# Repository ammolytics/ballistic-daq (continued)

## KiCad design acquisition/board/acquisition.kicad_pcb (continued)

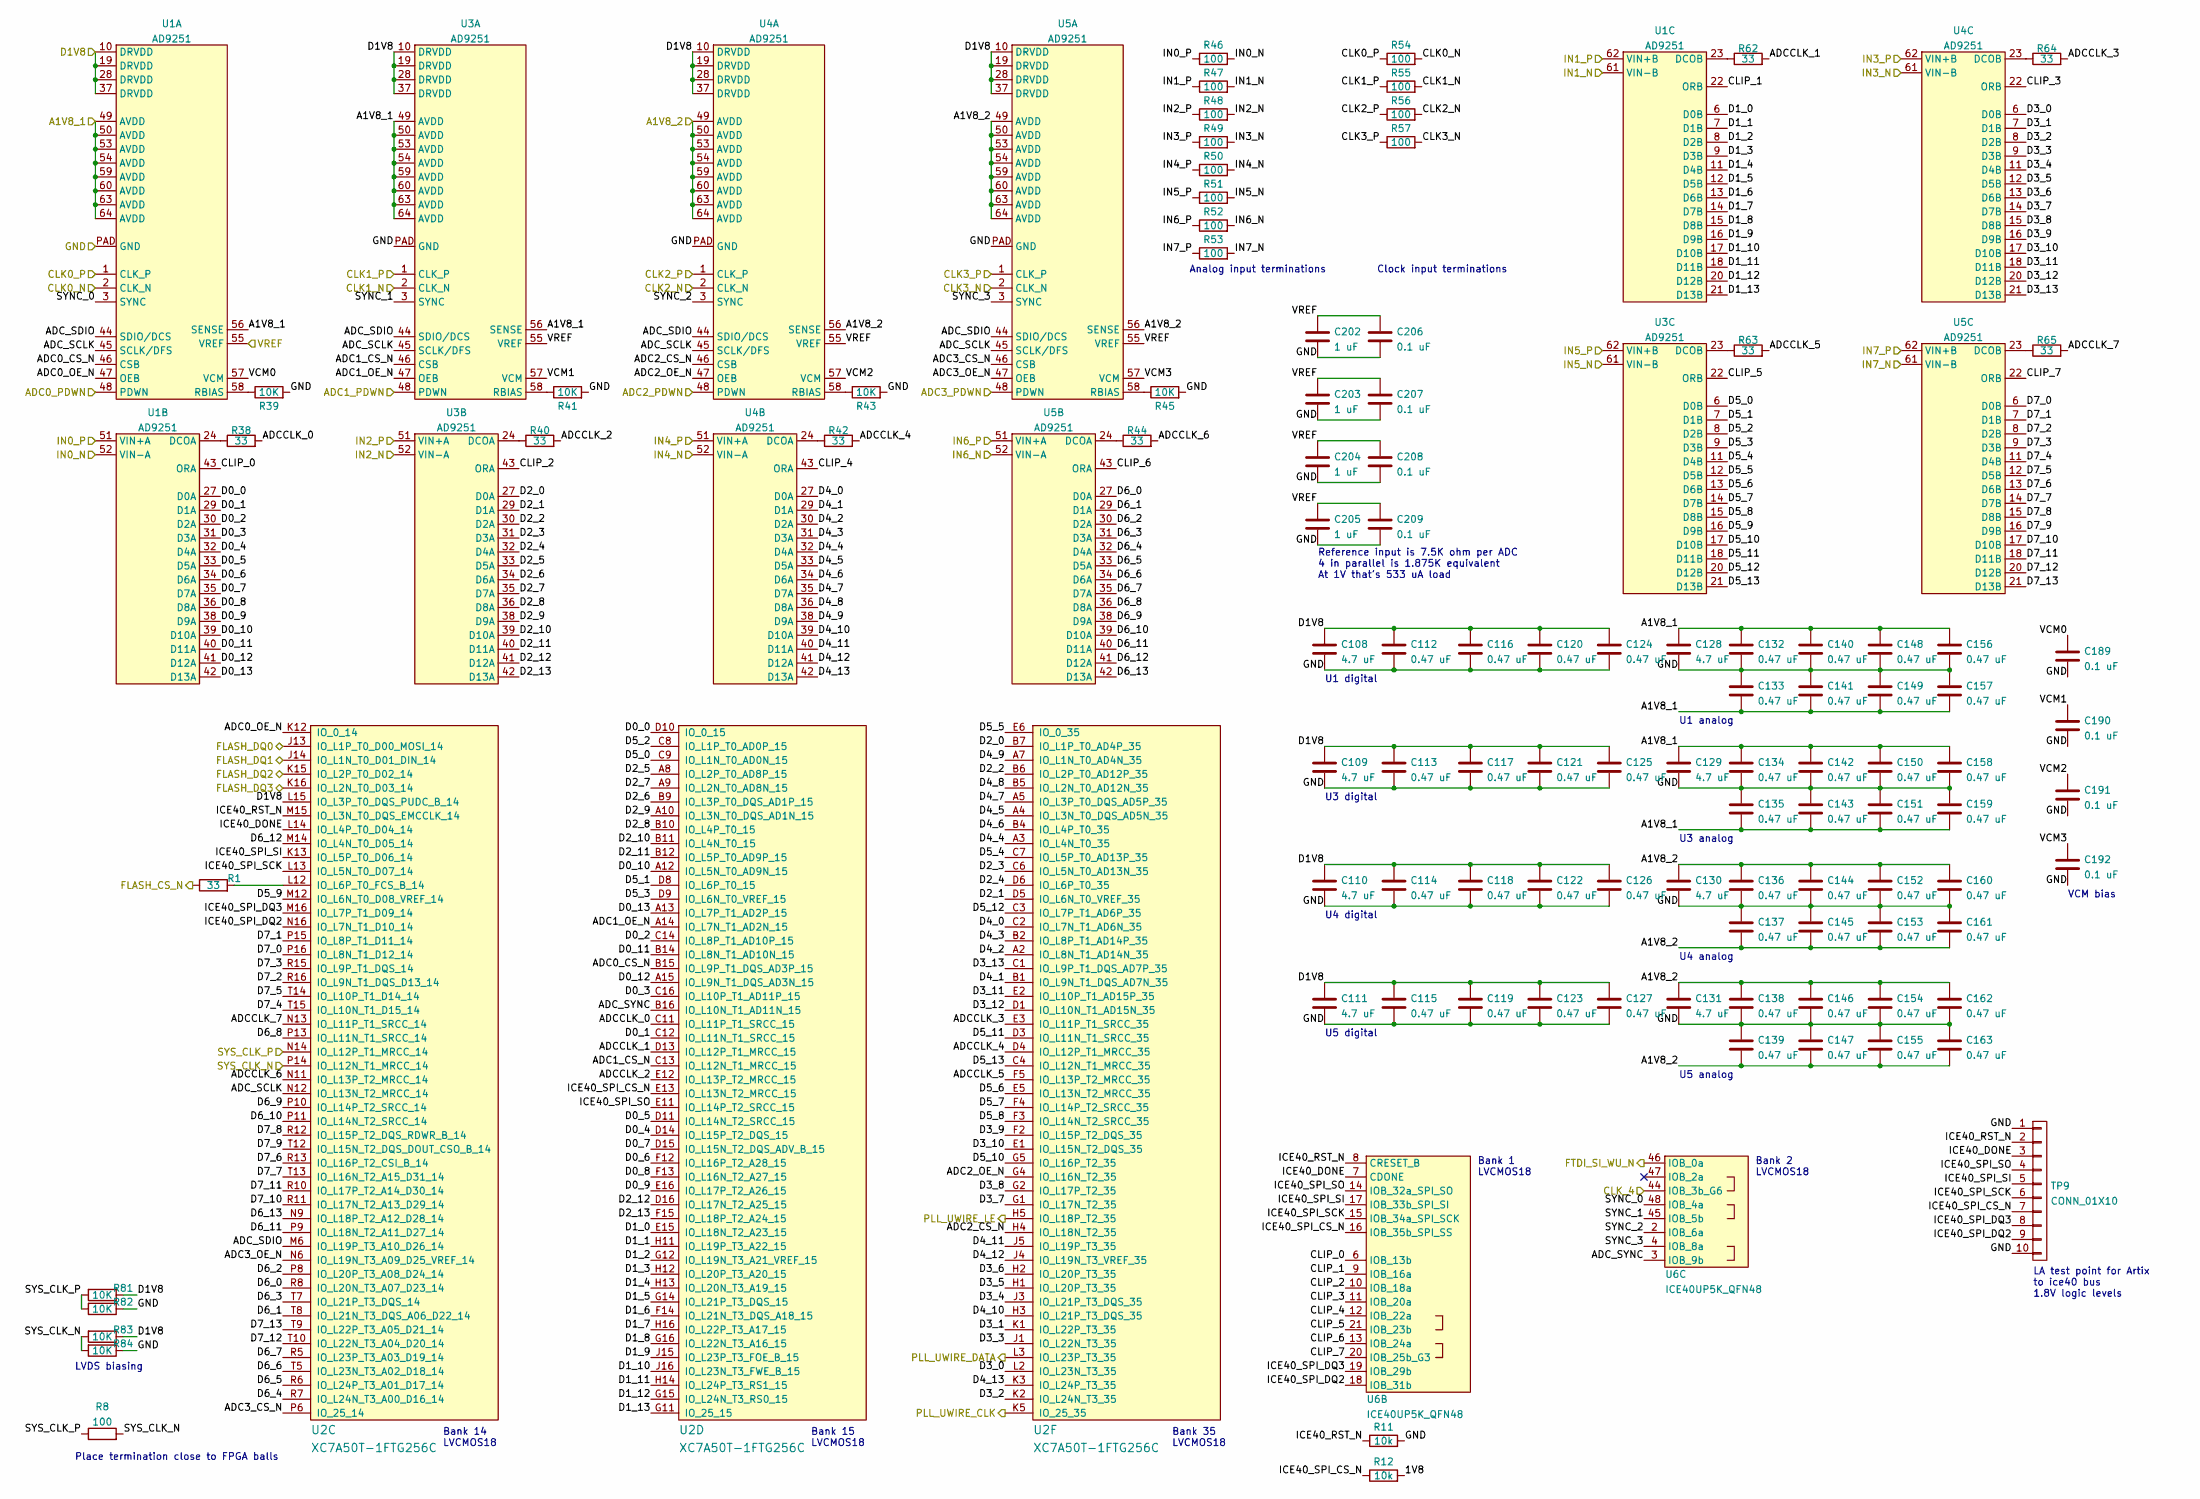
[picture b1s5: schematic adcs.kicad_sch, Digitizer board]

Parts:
C108, C109, C110, C111, C128, C129, C130, C131: 4.7 uF; EIA_0603_CAP_NOSILK
C112, C113, C114, C115, C116, C117, C118, C119, C120, C121, C122, C123, C124, C125, C126, C127, C132, C133, C134, C135, C136, C137, C138, C139, C140, C141, C142, C143, C144, C145, C146, C147, C148, C149, C150, C151, C152, C153, C154, C155, C156, C157, C158, C159, C160, C161, C162, C163: 0.47 uF; EIA_0402_CAP_NOSILK
C189, C190, C191, C192, C206, C207, C208, C209: 0.1 uF; EIA_0402_CAP_NOSILK
C202, C203, C204, C205: 1 uF; EIA_0603_CAP_NOSILK
R1, R38, R40, R42, R44, R62, R63, R64, R65: 33; EIA_0402_RES_NOSILK
R8, R46, R47, R48, R49, R50, R51, R52, R53, R54, R55, R56, R57: 100; EIA_0402_RES_NOSILK
R11, R12: 10k; EIA_0402_RES_NOSILK
R39, R41, R43, R45, R81, R82, R83, R84: 10K; EIA_0402_RES_NOSILK
TP9: CONN_01X10; CONN_HEADER_2.54MM_1x10
U1, U3, U4, U5: AD9251; QFN_64_0.5MM_9x9MM
U2: XC7A50T-1FTG256C; BGA_256_17x17_FULLARRAY_1MM_0.4MM_FTG256
U6: ICE40UP5K_QFN48; QFN_48_0.5MM_7x7MM

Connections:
/ADCs/1V8: R12.2
/ADCs/A1V8_1: C128.1, C129.1, C132.1, C133.2, C134.1, C135.2, C140.1, C141.2, C142.1, C143.2, C148.1, C149.2, C150.1, C151.2, C156.1, C157.2, C158.1, C159.2, U1.49 (AVDD), U1.50 (AVDD), U1.53 (AVDD), U1.54 (AVDD), U1.56 (SENSE), U1.59 (AVDD), U1.60 (AVDD), U1.63 (AVDD), U1.64 (AVDD), U3.49 (AVDD), U3.50 (AVDD), U3.53 (AVDD), U3.54 (AVDD), U3.56 (SENSE), U3.59 (AVDD), U3.60 (AVDD), U3.63 (AVDD), U3.64 (AVDD); also elsewhere on the board
/ADCs/A1V8_2: C130.1, C131.1, C136.1, C137.2, C138.1, C139.2, C144.1, C145.2, C146.1, C147.2, C152.1, C153.2, C154.1, C155.2, C160.1, C161.2, C162.1, C163.2, U4.49 (AVDD), U4.50 (AVDD), U4.53 (AVDD), U4.54 (AVDD), U4.56 (SENSE), U4.59 (AVDD), U4.60 (AVDD), U4.63 (AVDD), U4.64 (AVDD), U5.49 (AVDD), U5.50 (AVDD), U5.53 (AVDD), U5.54 (AVDD), U5.56 (SENSE), U5.59 (AVDD), U5.60 (AVDD), U5.63 (AVDD), U5.64 (AVDD); also elsewhere on the board
/ADCs/ADC0_CS_N: U1.46 (CSB), U2.B15 (IO_L9P_T1_DQS_AD3P_15)
/ADCs/ADC0_OE_N: U1.47 (OEB), U2.K12 (IO_0_14)
/ADCs/ADC1_CS_N: U2.C13 (IO_L12N_T1_MRCC_15), U3.46 (CSB)
/ADCs/ADC1_OE_N: U2.A14 (IO_L7N_T1_AD2N_15), U3.47 (OEB)
/ADCs/ADC2_CS_N: U2.H4 (IO_L18N_T2_35), U4.46 (CSB)
/ADCs/ADC2_OE_N: U2.G4 (IO_L16N_T2_35), U4.47 (OEB)
/ADCs/ADC3_CS_N: U2.P6 (IO_25_14), U5.46 (CSB)
/ADCs/ADC3_OE_N: U2.N6 (IO_L19N_T3_A09_D25_VREF_14), U5.47 (OEB)
/ADCs/ADCCLK_0: R38.2, U2.C11 (IO_L11P_T1_SRCC_15)
/ADCs/ADCCLK_1: R62.2, U2.D13 (IO_L12P_T1_MRCC_15)
/ADCs/ADCCLK_2: R40.2, U2.E12 (IO_L13P_T2_MRCC_15)
/ADCs/ADCCLK_3: R64.2, U2.E3 (IO_L11P_T1_SRCC_35)
/ADCs/ADCCLK_4: R42.2, U2.D4 (IO_L12P_T1_MRCC_35)
/ADCs/ADCCLK_5: R63.2, U2.F5 (IO_L13P_T2_MRCC_35)
/ADCs/ADCCLK_6: R44.2, U2.N11 (IO_L13P_T2_MRCC_14)
/ADCs/ADCCLK_7: R65.2, U2.N13 (IO_L11P_T1_SRCC_14)
/ADCs/ADC_SCLK: U1.45 (SCLK/DFS), U2.N12 (IO_L13N_T2_MRCC_14), U3.45 (SCLK/DFS), U4.45 (SCLK/DFS), U5.45 (SCLK/DFS)
/ADCs/ADC_SDIO: U1.44 (SDIO/DCS), U2.M6 (IO_L19P_T3_A10_D26_14), U3.44 (SDIO/DCS), U4.44 (SDIO/DCS), U5.44 (SDIO/DCS)
/ADCs/ADC_SYNC: U2.B16 (IO_L10N_T1_AD11N_15), U6.3 (IOB_9b)
/ADCs/CLIP_0: U1.43 (ORA), U6.6 (IOB_13b)
/ADCs/CLIP_1: U1.22 (ORB), U6.9 (IOB_16a)
/ADCs/CLIP_2: U3.43 (ORA), U6.10 (IOB_18a)
/ADCs/CLIP_3: U4.22 (ORB), U6.11 (IOB_20a)
/ADCs/CLIP_4: U4.43 (ORA), U6.12 (IOB_22a)
/ADCs/CLIP_5: U3.22 (ORB), U6.21 (IOB_23b)
/ADCs/CLIP_6: U5.43 (ORA), U6.13 (IOB_24a)
/ADCs/CLIP_7: U5.22 (ORB), U6.20 (IOB_25b_G3)
/ADCs/CLK0_N: R54.2, U1.2 (CLK_N); also elsewhere on the board
/ADCs/CLK0_P: R54.1, U1.1 (CLK_P); also elsewhere on the board
/ADCs/CLK1_N: R55.2, U3.2 (CLK_N); also elsewhere on the board
/ADCs/CLK1_P: R55.1, U3.1 (CLK_P); also elsewhere on the board
/ADCs/CLK2_N: R56.2, U4.2 (CLK_N); also elsewhere on the board
/ADCs/CLK2_P: R56.1, U4.1 (CLK_P); also elsewhere on the board
/ADCs/CLK3_N: R57.2, U5.2 (CLK_N); also elsewhere on the board
/ADCs/CLK3_P: R57.1, U5.1 (CLK_P); also elsewhere on the board
/ADCs/D0_0: U1.27 (D0A), U2.D10 (IO_0_15)
/ADCs/D0_1: U1.29 (D1A), U2.C12 (IO_L11N_T1_SRCC_15)
/ADCs/D0_2: U1.30 (D2A), U2.C14 (IO_L8P_T1_AD10P_15)
/ADCs/D0_3: U1.31 (D3A), U2.C16 (IO_L10P_T1_AD11P_15)
/ADCs/D0_4: U1.32 (D4A), U2.D14 (IO_L15P_T2_DQS_15)
/ADCs/D0_5: U1.33 (D5A), U2.D11 (IO_L14N_T2_SRCC_15)
/ADCs/D0_6: U1.34 (D6A), U2.F12 (IO_L16P_T2_A28_15)
/ADCs/D0_7: U1.35 (D7A), U2.D15 (IO_L15N_T2_DQS_ADV_B_15)
/ADCs/D0_8: U1.36 (D8A), U2.F13 (IO_L16N_T2_A27_15)
/ADCs/D0_9: U1.38 (D9A), U2.E16 (IO_L17P_T2_A26_15)
/ADCs/D0_10: U1.39 (D10A), U2.A12 (IO_L5N_T0_AD9N_15)
/ADCs/D0_11: U1.40 (D11A), U2.B14 (IO_L8N_T1_AD10N_15)
/ADCs/D0_12: U1.41 (D12A), U2.A15 (IO_L9N_T1_DQS_AD3N_15)
/ADCs/D0_13: U1.42 (D13A), U2.A13 (IO_L7P_T1_AD2P_15)
/ADCs/D1_0: U1.6 (D0B), U2.E15 (IO_L18N_T2_A23_15)
/ADCs/D1_1: U1.7 (D1B), U2.H11 (IO_L19P_T3_A22_15)
/ADCs/D1_2: U1.8 (D2B), U2.G12 (IO_L19N_T3_A21_VREF_15)
/ADCs/D1_3: U1.9 (D3B), U2.H12 (IO_L20P_T3_A20_15)
/ADCs/D1_4: U1.11 (D4B), U2.H13 (IO_L20N_T3_A19_15)
/ADCs/D1_5: U1.12 (D5B), U2.G14 (IO_L21P_T3_DQS_15)
/ADCs/D1_6: U1.13 (D6B), U2.F14 (IO_L21N_T3_DQS_A18_15)
/ADCs/D1_7: U1.14 (D7B), U2.H16 (IO_L22P_T3_A17_15)
/ADCs/D1_8: U1.15 (D8B), U2.G16 (IO_L22N_T3_A16_15)
/ADCs/D1_9: U1.16 (D9B), U2.J15 (IO_L23P_T3_FOE_B_15)
/ADCs/D1_10: U1.17 (D10B), U2.J16 (IO_L23N_T3_FWE_B_15)
/ADCs/D1_11: U1.18 (D11B), U2.H14 (IO_L24P_T3_RS1_15)
/ADCs/D1_12: U1.20 (D12B), U2.G15 (IO_L24N_T3_RS0_15)
/ADCs/D1_13: U1.21 (D13B), U2.G11 (IO_25_15)
/ADCs/D2_0: U2.B7 (IO_L1P_T0_AD4P_35), U3.27 (D0A)
/ADCs/D2_1: U2.D5 (IO_L6N_T0_VREF_35), U3.29 (D1A)
/ADCs/D2_2: U2.B6 (IO_L2P_T0_AD12P_35), U3.30 (D2A)
/ADCs/D2_3: U2.C6 (IO_L5N_T0_AD13N_35), U3.31 (D3A)
/ADCs/D2_4: U2.D6 (IO_L6P_T0_35), U3.32 (D4A)
/ADCs/D2_5: U2.A8 (IO_L2P_T0_AD8P_15), U3.33 (D5A)
/ADCs/D2_6: U2.B9 (IO_L3P_T0_DQS_AD1P_15), U3.34 (D6A)
/ADCs/D2_7: U2.A9 (IO_L2N_T0_AD8N_15), U3.35 (D7A)
/ADCs/D2_8: U2.B10 (IO_L4P_T0_15), U3.36 (D8A)
/ADCs/D2_9: U2.A10 (IO_L3N_T0_DQS_AD1N_15), U3.38 (D9A)
/ADCs/D2_10: U2.B11 (IO_L4N_T0_15), U3.39 (D10A)
/ADCs/D2_11: U2.B12 (IO_L5P_T0_AD9P_15), U3.40 (D11A)
/ADCs/D2_12: U2.D16 (IO_L17N_T2_A25_15), U3.41 (D12A)
/ADCs/D2_13: U2.F15 (IO_L18P_T2_A24_15), U3.42 (D13A)
/ADCs/D3_0: U2.L2 (IO_L23N_T3_35), U4.6 (D0B)
/ADCs/D3_1: U2.K1 (IO_L22P_T3_35), U4.7 (D1B)
/ADCs/D3_2: U2.K2 (IO_L24N_T3_35), U4.8 (D2B)
/ADCs/D3_3: U2.J1 (IO_L22N_T3_35), U4.9 (D3B)
/ADCs/D3_4: U2.J3 (IO_L21P_T3_DQS_35), U4.11 (D4B)
/ADCs/D3_5: U2.H1 (IO_L20P_T3_35), U4.12 (D5B)
/ADCs/D3_6: U2.H2 (IO_L20P_T3_35), U4.13 (D6B)
/ADCs/D3_7: U2.G1 (IO_L17N_T2_35), U4.14 (D7B)
/ADCs/D3_8: U2.G2 (IO_L17P_T2_35), U4.15 (D8B)
/ADCs/D3_9: U2.F2 (IO_L15P_T2_DQS_35), U4.16 (D9B)
/ADCs/D3_10: U2.E1 (IO_L15N_T2_DQS_35), U4.17 (D10B)
/ADCs/D3_11: U2.E2 (IO_L10P_T1_AD15P_35), U4.18 (D11B)
/ADCs/D3_12: U2.D1 (IO_L10N_T1_AD15N_35), U4.20 (D12B)
/ADCs/D3_13: U2.C1 (IO_L9P_T1_DQS_AD7P_35), U4.21 (D13B)
/ADCs/D4_0: U2.C2 (IO_L7N_T1_AD6N_35), U4.27 (D0A)
/ADCs/D4_1: U2.B1 (IO_L9N_T1_DQS_AD7N_35), U4.29 (D1A)
/ADCs/D4_2: U2.A2 (IO_L8N_T1_AD14N_35), U4.30 (D2A)
/ADCs/D4_3: U2.B2 (IO_L8P_T1_AD14P_35), U4.31 (D3A)
/ADCs/D4_4: U2.A3 (IO_L4N_T0_35), U4.32 (D4A)
/ADCs/D4_5: U2.A4 (IO_L3N_T0_DQS_AD5N_35), U4.33 (D5A)
/ADCs/D4_6: U2.B4 (IO_L4P_T0_35), U4.34 (D6A)
/ADCs/D4_7: U2.A5 (IO_L3P_T0_DQS_AD5P_35), U4.35 (D7A)
/ADCs/D4_8: U2.B5 (IO_L2N_T0_AD12N_35), U4.36 (D8A)
/ADCs/D4_9: U2.A7 (IO_L1N_T0_AD4N_35), U4.38 (D9A)
/ADCs/D4_10: U2.H3 (IO_L21P_T3_DQS_35), U4.39 (D10A)
/ADCs/D4_11: U2.J5 (IO_L19P_T3_35), U4.40 (D11A)
/ADCs/D4_12: U2.J4 (IO_L19N_T3_VREF_35), U4.41 (D12A)
/ADCs/D4_13: U2.K3 (IO_L24P_T3_35), U4.42 (D13A)
/ADCs/D5_0: U2.C9 (IO_L1N_T0_AD0N_15), U3.6 (D0B)
/ADCs/D5_1: U2.D8 (IO_L6P_T0_15), U3.7 (D1B)
/ADCs/D5_2: U2.C8 (IO_L1P_T0_AD0P_15), U3.8 (D2B)
/ADCs/D5_3: U2.D9 (IO_L6N_T0_VREF_15), U3.9 (D3B)
/ADCs/D5_4: U2.C7 (IO_L5P_T0_AD13P_35), U3.11 (D4B)
/ADCs/D5_5: U2.E6 (IO_0_35), U3.12 (D5B)
/ADCs/D5_6: U2.E5 (IO_L13N_T2_MRCC_35), U3.13 (D6B)
/ADCs/D5_7: U2.F4 (IO_L14P_T2_SRCC_35), U3.14 (D7B)
/ADCs/D5_8: U2.F3 (IO_L14N_T2_SRCC_35), U3.15 (D8B)
/ADCs/D5_9: U2.M12 (IO_L6N_T0_D08_VREF_14), U3.16 (D9B)
/ADCs/D5_10: U2.G5 (IO_L16P_T2_35), U3.17 (D10B)
/ADCs/D5_11: U2.D3 (IO_L11N_T1_SRCC_35), U3.18 (D11B)
/ADCs/D5_12: U2.C3 (IO_L7P_T1_AD6P_35), U3.20 (D12B)
/ADCs/D5_13: U2.C4 (IO_L12N_T1_MRCC_35), U3.21 (D13B)
/ADCs/D6_0: U2.R8 (IO_L20N_T3_A07_D23_14), U5.27 (D0A)
/ADCs/D6_1: U2.T8 (IO_L21N_T3_DQS_A06_D22_14), U5.29 (D1A)
/ADCs/D6_2: U2.P8 (IO_L20P_T3_A08_D24_14), U5.30 (D2A)
/ADCs/D6_3: U2.T7 (IO_L21P_T3_DQS_14), U5.31 (D3A)
/ADCs/D6_4: U2.R7 (IO_L24N_T3_A00_D16_14), U5.32 (D4A)
/ADCs/D6_5: U2.R6 (IO_L24P_T3_A01_D17_14), U5.33 (D5A)
/ADCs/D6_6: U2.T5 (IO_L23N_T3_A02_D18_14), U5.34 (D6A)
/ADCs/D6_7: U2.R5 (IO_L23P_T3_A03_D19_14), U5.35 (D7A)
/ADCs/D6_8: U2.P13 (IO_L11N_T1_SRCC_14), U5.36 (D8A)
/ADCs/D6_9: U2.P10 (IO_L14P_T2_SRCC_14), U5.38 (D9A)
/ADCs/D6_10: U2.P11 (IO_L14N_T2_SRCC_14), U5.39 (D10A)
/ADCs/D6_11: U2.P9 (IO_L18N_T2_A11_D27_14), U5.40 (D11A)
/ADCs/D6_12: U2.M14 (IO_L4N_T0_D05_14), U5.41 (D12A)
/ADCs/D6_13: U2.N9 (IO_L18P_T2_A12_D28_14), U5.42 (D13A)
/ADCs/D7_0: U2.P16 (IO_L8N_T1_D12_14), U5.6 (D0B)
/ADCs/D7_1: U2.P15 (IO_L8P_T1_D11_14), U5.7 (D1B)
/ADCs/D7_2: U2.R16 (IO_L9N_T1_DQS_D13_14), U5.8 (D2B)
/ADCs/D7_3: U2.R15 (IO_L9P_T1_DQS_14), U5.9 (D3B)
/ADCs/D7_4: U2.T15 (IO_L10N_T1_D15_14), U5.11 (D4B)
/ADCs/D7_5: U2.T14 (IO_L10P_T1_D14_14), U5.12 (D5B)
/ADCs/D7_6: U2.R13 (IO_L16P_T2_CSI_B_14), U5.13 (D6B)
/ADCs/D7_7: U2.T13 (IO_L16N_T2_A15_D31_14), U5.14 (D7B)
/ADCs/D7_8: U2.R12 (IO_L15P_T2_DQS_RDWR_B_14), U5.15 (D8B)
/ADCs/D7_9: U2.T12 (IO_L15N_T2_DQS_DOUT_CSO_B_14), U5.16 (D9B)
/ADCs/D7_10: U2.R11 (IO_L17N_T2_A13_D29_14), U5.17 (D10B)
/ADCs/D7_11: U2.R10 (IO_L17P_T2_A14_D30_14), U5.18 (D11B)
/ADCs/D7_12: U2.T10 (IO_L22N_T3_A04_D20_14), U5.20 (D12B)
/ADCs/D7_13: U2.T9 (IO_L22P_T3_A05_D21_14), U5.21 (D13B)
/ADCs/FLASH_DQ0: U2.J13 (IO_L1P_T0_D00_MOSI_14); also elsewhere on the board
/ADCs/FLASH_DQ1: U2.J14 (IO_L1N_T0_D01_DIN_14); also elsewhere on the board
/ADCs/FLASH_DQ2: U2.K15 (IO_L2P_T0_D02_14); also elsewhere on the board
/ADCs/FLASH_DQ3: U2.K16 (IO_L2N_T0_D03_14); also elsewhere on the board
/ADCs/FTDI_SI_WU_N: U6.46 (IOB_0a); also elsewhere on the board
/ADCs/ICE40_DONE: TP9.3, U2.L14 (IO_L4P_T0_D04_14), U6.7 (CDONE)
/ADCs/ICE40_RST_N: R11.1, TP9.2, U2.M15 (IO_L3N_T0_DQS_EMCCLK_14), U6.8 (CRESET_B)
/ADCs/ICE40_SPI_CS_N: R12.1, TP9.7, U2.E13 (IO_L13N_T2_MRCC_15), U6.16 (IOB_35b_SPI_SS)
/ADCs/ICE40_SPI_DQ2: TP9.9, U2.N16 (IO_L7N_T1_D10_14), U6.18 (IOB_31b)
/ADCs/ICE40_SPI_DQ3: TP9.8, U2.M16 (IO_L7P_T1_D09_14), U6.19 (IOB_29b)
/ADCs/ICE40_SPI_SCK: TP9.6, U2.L13 (IO_L5N_T0_D07_14), U6.15 (IOB_34a_SPI_SCK)
/ADCs/ICE40_SPI_SI: TP9.5, U2.K13 (IO_L5P_T0_D06_14), U6.17 (IOB_33b_SPI_SI)
/ADCs/ICE40_SPI_SO: TP9.4, U2.E11 (IO_L14P_T2_SRCC_15), U6.14 (IOB_32a_SPI_SO)
/ADCs/IN0_N: R46.2, U1.52 (VIN-A); also elsewhere on the board
/ADCs/IN0_P: R46.1, U1.51 (VIN+A); also elsewhere on the board
/ADCs/IN1_N: R47.2, U1.61 (VIN-B); also elsewhere on the board
/ADCs/IN1_P: R47.1, U1.62 (VIN+B); also elsewhere on the board
/ADCs/IN2_N: R48.2, U3.52 (VIN-A); also elsewhere on the board
/ADCs/IN2_P: R48.1, U3.51 (VIN+A); also elsewhere on the board
/ADCs/IN3_N: R49.2, U4.61 (VIN-B); also elsewhere on the board
/ADCs/IN3_P: R49.1, U4.62 (VIN+B); also elsewhere on the board
/ADCs/IN4_N: R50.2, U4.52 (VIN-A); also elsewhere on the board
/ADCs/IN4_P: R50.1, U4.51 (VIN+A); also elsewhere on the board
/ADCs/IN5_N: R51.2, U3.61 (VIN-B); also elsewhere on the board
/ADCs/IN5_P: R51.1, U3.62 (VIN+B); also elsewhere on the board
/ADCs/IN6_N: R52.2, U5.52 (VIN-A); also elsewhere on the board
/ADCs/IN6_P: R52.1, U5.51 (VIN+A); also elsewhere on the board
/ADCs/IN7_N: R53.2, U5.61 (VIN-B); also elsewhere on the board
/ADCs/IN7_P: R53.1, U5.62 (VIN+B); also elsewhere on the board
/ADCs/PLL_UWIRE_CLK: U2.K5 (IO_25_35); also elsewhere on the board
/ADCs/PLL_UWIRE_DATA: U2.L3 (IO_L23P_T3_35); also elsewhere on the board
/ADCs/PLL_UWIRE_LE: U2.H5 (IO_L18P_T2_35); also elsewhere on the board
/ADCs/SYNC_0: U1.3 (SYNC), U6.48 (IOB_4a)
/ADCs/SYNC_1: U3.3 (SYNC), U6.45 (IOB_5b)
/ADCs/SYNC_2: U4.3 (SYNC), U6.2 (IOB_6a)
/ADCs/SYNC_3: U5.3 (SYNC), U6.4 (IOB_8a)
/ADCs/SYS_CLK_N: R8.2, R83.2, R84.2, U2.P14 (IO_L12N_T1_MRCC_14); also elsewhere on the board
/ADCs/SYS_CLK_P: R8.1, R81.2, R82.2, U2.N14 (IO_L12P_T1_MRCC_14); also elsewhere on the board
/ADCs/VCM0: C189.1, U1.57 (VCM)
/ADCs/VCM1: C190.1, U3.57 (VCM)
/ADCs/VCM2: C191.1, U4.57 (VCM)
/ADCs/VCM3: C192.1, U5.57 (VCM)
/CLK_4: U6.44 (IOB_3b_G6); also elsewhere on the board
/D1V8: C108.1, C109.1, C110.1, C111.1, C112.1, C113.1, C114.1, C115.1, C116.1, C117.1, C118.1, C119.1, C120.1, C121.1, C122.1, C123.1, C124.1, C125.1, C126.1, C127.1, R81.1, R83.1, U1.10 (DRVDD), U1.19 (DRVDD), U1.28 (DRVDD), U1.37 (DRVDD), U2.L15 (IO_L3P_T0_DQS_PUDC_B_14), U3.10 (DRVDD), U3.19 (DRVDD), U3.28 (DRVDD), U3.37 (DRVDD), U4.10 (DRVDD), U4.19 (DRVDD), U4.28 (DRVDD), U4.37 (DRVDD), U5.10 (DRVDD), U5.19 (DRVDD), U5.28 (DRVDD), U5.37 (DRVDD); also elsewhere on the board
/GND: C108.2, C109.2, C110.2, C111.2, C112.2, C113.2, C114.2, C115.2, C116.2, C117.2, C118.2, C119.2, C120.2, C121.2, C122.2, C123.2, C124.2, C125.2, C126.2, C127.2, C128.2, C129.2, C130.2, C131.2, C132.2, C133.1, C134.2, C135.1, C136.2, C137.1, C138.2, C139.1, C140.2, C141.1, C142.2, C143.1, C144.2, C145.1, C146.2, C147.1, C148.2, C149.1, C150.2, C151.1, C152.2, C153.1, C154.2, C155.1, C156.2, C157.1, C158.2, C159.1, C160.2, C161.1, C162.2, C163.1, C189.2, C190.2, C191.2, C192.2, C202.2, C203.2, C204.2, C205.2, C206.2, C207.2, C208.2, C209.2, R11.2, R39.2, R41.2, R43.2, R45.2, R82.1, R84.1, TP9.1, TP9.10, U1.PAD (GND), U3.PAD (GND), U4.PAD (GND), U5.PAD (GND); also elsewhere on the board
/MCU/ADC0_PDWN: U1.48 (PDWN); also elsewhere on the board
/MCU/ADC1_PDWN: U3.48 (PDWN); also elsewhere on the board
/MCU/ADC2_PDWN: U4.48 (PDWN); also elsewhere on the board
/MCU/ADC3_PDWN: U5.48 (PDWN); also elsewhere on the board
/QSPI flash/FLASH_CS_N: R1.1; also elsewhere on the board
/VREF: C202.1, C203.1, C204.1, C205.1, C206.1, C207.1, C208.1, C209.1, U1.55 (VREF), U3.55 (VREF), U4.55 (VREF), U5.55 (VREF); also elsewhere on the board
unnamed: R1.2, U2.L12 (IO_L6P_T0_FCS_B_14)
unnamed: R38.1, U1.24 (DCOA)
unnamed: R39.1, U1.58 (RBIAS)
unnamed: R40.1, U3.24 (DCOA)
unnamed: R41.1, U3.58 (RBIAS)
unnamed: R42.1, U4.24 (DCOA)
unnamed: R43.1, U4.58 (RBIAS)
unnamed: R44.1, U5.24 (DCOA)
unnamed: R45.1, U5.58 (RBIAS)
unnamed: R62.1, U1.23 (DCOB)
unnamed: R63.1, U3.23 (DCOB)
unnamed: R64.1, U4.23 (DCOB)
unnamed: R65.1, U5.23 (DCOB)

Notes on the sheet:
Bank 35 LVCMOS18
U5 analog
Bank 15 LVCMOS18
LVDS biasing
Bank 2 LVCMOS18
Bank 14 LVCMOS18
U4 analog
U4 digital
Analog input terminations
Clock input terminations
Bank 1 LVCMOS18
Place termination close to FPGA balls
VCM bias
U3 analog
Reference input is 7.5K ohm per ADC 4 in parallel is 1.875K equivalent At 1V that's 533 uA load
LA test point for Artix to ice40 bus 1.8V logic levels
U1 digital
U3 digital
U5 digital
U1 analog

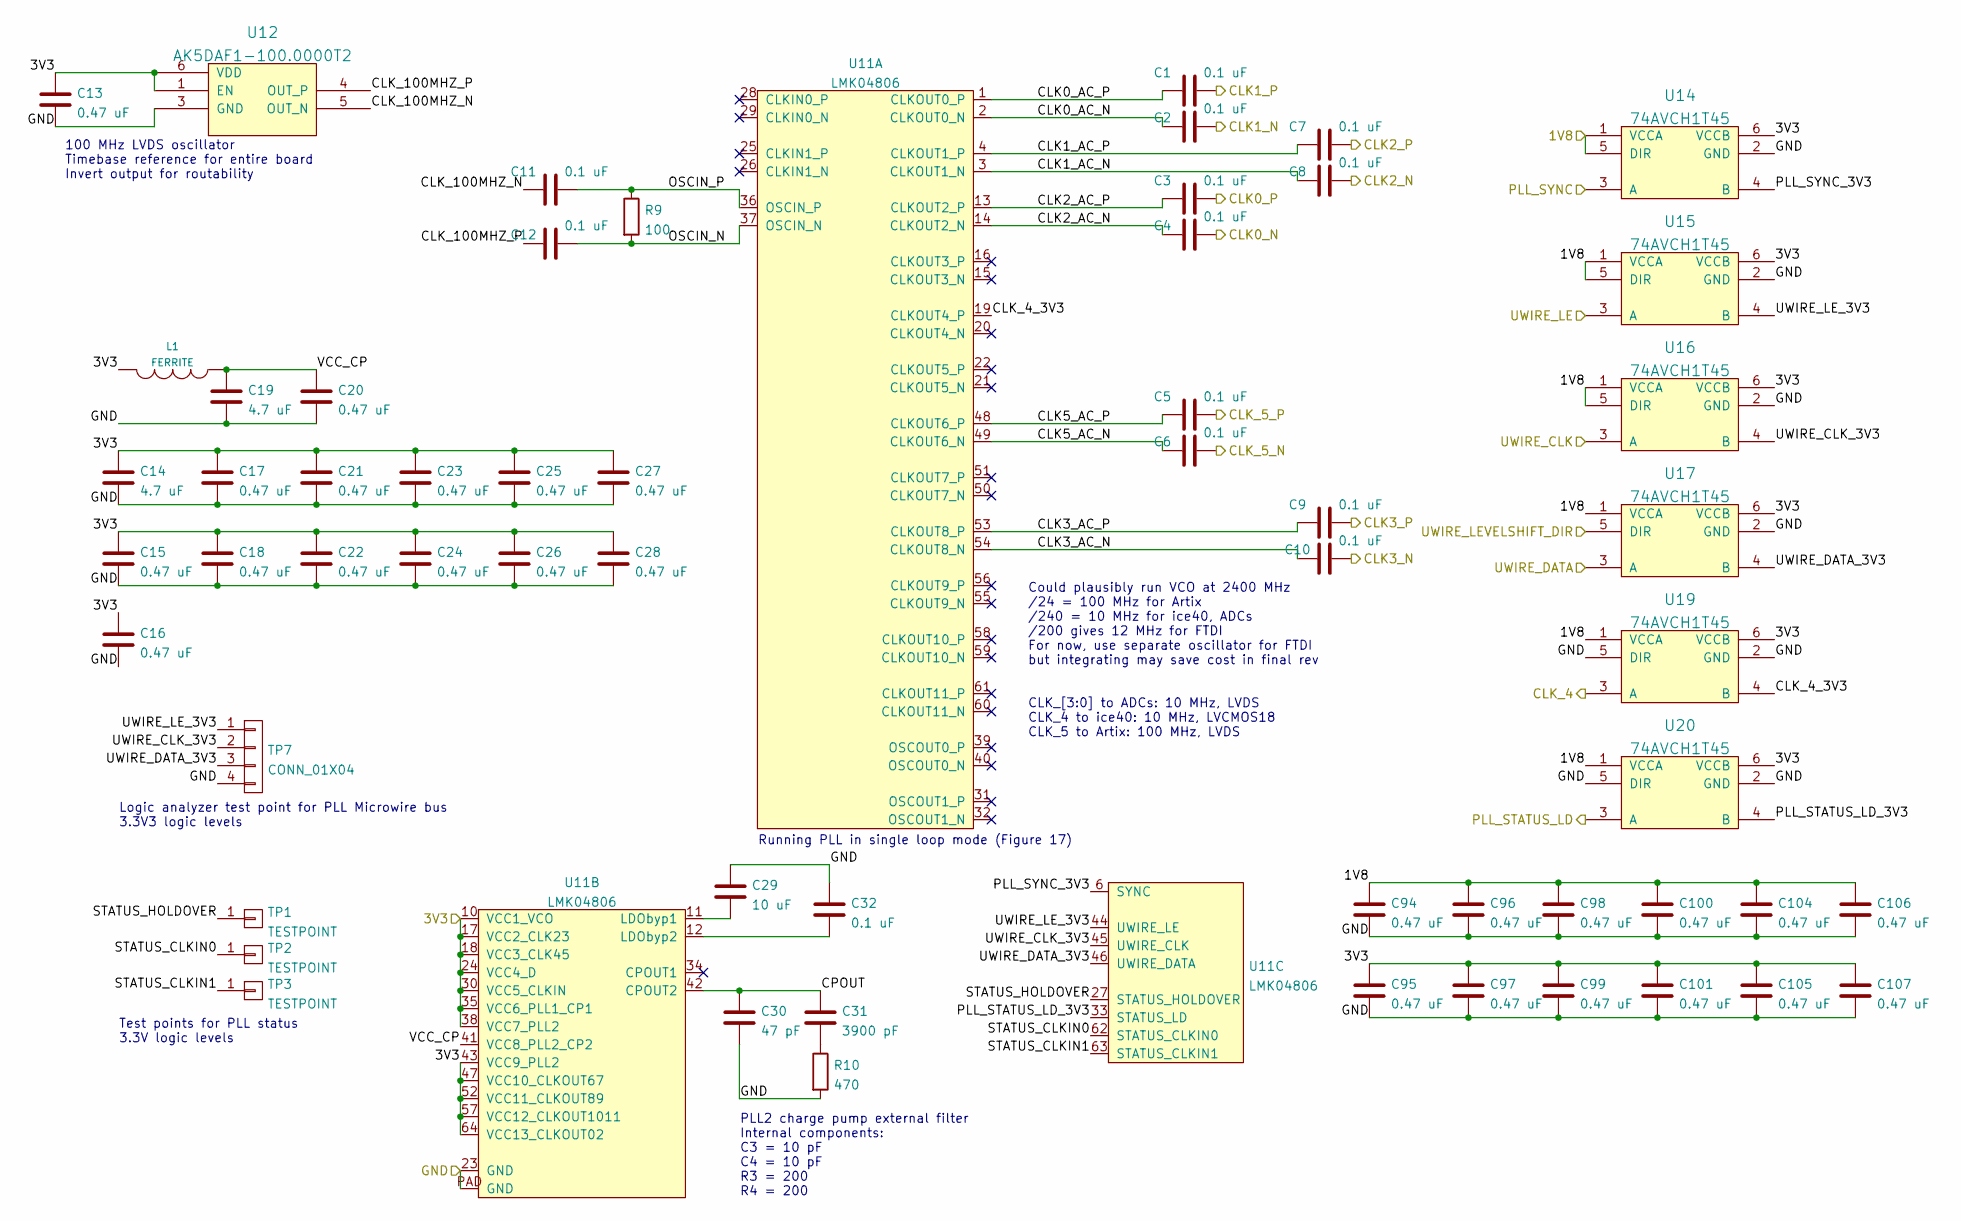
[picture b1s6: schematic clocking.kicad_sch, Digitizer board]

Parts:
C1, C2, C3, C4, C5, C6, C7, C8, C9, C10, C11, C12, C32: 0.1 uF; EIA_0402_CAP_NOSILK
C13, C15, C16, C17, C18, C20, C21, C22, C23, C24, C25, C26, C27, C28, C94, C95, C96, C97, C98, C99, C100, C101, C104, C105, C106, C107: 0.47 uF; EIA_0402_CAP_NOSILK
C14, C19: 4.7 uF; EIA_0603_CAP_NOSILK
C29: 10 uF; EIA_0805_CAP_NOSILK
C30: 47 pF; EIA_0402_CAP_NOSILK
C31: 3900 pF; EIA_0402_CAP_NOSILK
L1: FERRITE; EIA_0603_INDUCTOR_NOSILK
R9: 100; EIA_0402_RES_NOSILK
R10: 470; EIA_0402_RES_NOSILK
TP1, TP2, TP3: TESTPOINT; TESTPOINT_SMT_0.5MM
TP7: CONN_01X04; CONN_HEADER_2.54MM_1x4
U11: LMK04806; QFN_64_0.5MM_9x9MM
U12: AK5DAF1-100.0000T2; OSCILLATOR_LVDS_5.0x3.2
U14, U15, U16, U17, U19, U20: 74AVCH1T45; DFN_6_0.5MM_1.45x1.00MM

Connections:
/3V3: C13.1, C14.1, C15.1, C16.1, C17.1, C18.1, C21.1, C22.1, C23.1, C24.1, C25.1, C26.1, C27.1, C28.1, C95.1, C97.1, C99.1, C101.1, C105.1, C107.1, L1.2, U11.10 (VCC1_VCO), U11.17 (VCC2_CLK23), U11.18 (VCC3_CLK45), U11.24 (VCC4_D), U11.30 (VCC5_CLKIN), U11.35 (VCC6_PLL1_CP1), U11.38 (VCC7_PLL2), U11.43 (VCC9_PLL2), U11.47 (VCC10_CLKOUT67), U11.52 (VCC11_CLKOUT89), U11.57 (VCC12_CLKOUT1011), U11.64 (VCC13_CLKOUT02), U12.1 (EN), U12.6 (VDD), U14.6 (VCCB), U15.6 (VCCB), U16.6 (VCCB), U17.6 (VCCB), U19.6 (VCCB), U20.6 (VCCB); also elsewhere on the board
/ADCs/CLK0_N: C4.2; also elsewhere on the board
/ADCs/CLK0_P: C3.2; also elsewhere on the board
/ADCs/CLK1_N: C2.2; also elsewhere on the board
/ADCs/CLK1_P: C1.2; also elsewhere on the board
/ADCs/CLK2_N: C8.2; also elsewhere on the board
/ADCs/CLK2_P: C7.2; also elsewhere on the board
/ADCs/CLK3_N: C10.2; also elsewhere on the board
/ADCs/CLK3_P: C9.2; also elsewhere on the board
/ADCs/PLL_UWIRE_CLK: U16.3 (A); also elsewhere on the board
/ADCs/PLL_UWIRE_DATA: U17.3 (A); also elsewhere on the board
/ADCs/PLL_UWIRE_LE: U15.3 (A); also elsewhere on the board
/ADCs/SYS_CLK_N: C6.2; also elsewhere on the board
/ADCs/SYS_CLK_P: C5.2; also elsewhere on the board
/CLK_4: U19.3 (A); also elsewhere on the board
/Clocking/CLK0_AC_N: C2.1, U11.2 (CLKOUT0_N)
/Clocking/CLK0_AC_P: C1.1, U11.1 (CLKOUT0_P)
/Clocking/CLK1_AC_N: C8.1, U11.3 (CLKOUT1_N)
/Clocking/CLK1_AC_P: C7.1, U11.4 (CLKOUT1_P)
/Clocking/CLK2_AC_N: C4.1, U11.14 (CLKOUT2_N)
/Clocking/CLK2_AC_P: C3.1, U11.13 (CLKOUT2_P)
/Clocking/CLK3_AC_N: C10.1, U11.54 (CLKOUT8_N)
/Clocking/CLK3_AC_P: C9.1, U11.53 (CLKOUT8_P)
/Clocking/CLK5_AC_N: C6.1, U11.49 (CLKOUT6_N)
/Clocking/CLK5_AC_P: C5.1, U11.48 (CLKOUT6_P)
/Clocking/CLK_4_3V3: U11.19 (CLKOUT4_P), U19.4 (B)
/Clocking/CLK_100MHZ_N: C11.1, U12.5 (OUT_N)
/Clocking/CLK_100MHZ_P: C12.1, U12.4 (OUT_P)
/Clocking/CPOUT: C30.1, C31.1, U11.42 (CPOUT2)
/Clocking/OSCIN_N: C12.2, R9.2, U11.37 (OSCIN_N)
/Clocking/OSCIN_P: C11.2, R9.1, U11.36 (OSCIN_P)
/Clocking/PLL_STATUS_LD_3V3: U11.33 (STATUS_LD), U20.4 (B)
/Clocking/PLL_SYNC_3V3: U11.6 (SYNC), U14.4 (B)
/Clocking/STATUS_CLKIN0: TP2.1, U11.62 (STATUS_CLKIN0)
/Clocking/STATUS_CLKIN1: TP3.1, U11.63 (STATUS_CLKIN1)
/Clocking/STATUS_HOLDOVER: TP1.1, U11.27 (STATUS_HOLDOVER)
/Clocking/UWIRE_CLK_3V3: TP7.2, U11.45 (UWIRE_CLK), U16.4 (B)
/Clocking/UWIRE_DATA_3V3: TP7.3, U11.46 (UWIRE_DATA), U17.4 (B)
/Clocking/UWIRE_LE_3V3: TP7.1, U11.44 (UWIRE_LE), U15.4 (B)
/Clocking/VCC_CP: C19.1, C20.1, L1.1, U11.41 (VCC8_PLL2_CP2)
/D1V8: C94.1, C96.1, C98.1, C100.1, C104.1, C106.1, U14.1 (VCCA), U14.5 (DIR), U15.1 (VCCA), U15.5 (DIR), U16.1 (VCCA), U16.5 (DIR), U17.1 (VCCA), U19.1 (VCCA), U20.1 (VCCA); also elsewhere on the board
/GND: C13.2, C14.2, C15.2, C16.2, C17.2, C18.2, C19.2, C20.2, C21.2, C22.2, C23.2, C24.2, C25.2, C26.2, C27.2, C28.2, C29.1, C30.2, C32.1, C94.2, C95.2, C96.2, C97.2, C98.2, C99.2, C100.2, C101.2, C104.2, C105.2, C106.2, C107.2, R10.2, TP7.4, U11.23 (GND), U11.PAD (GND), U12.3 (GND), U14.2 (GND), U15.2 (GND), U16.2 (GND), U17.2 (GND), U19.2 (GND), U19.5 (DIR), U20.2 (GND), U20.5 (DIR); also elsewhere on the board
/PLL_STATUS_LD: U20.3 (A); also elsewhere on the board
/PLL_SYNC: U14.3 (A); also elsewhere on the board
/UWIRE_LEVELSHIFT_DIR: U17.5 (DIR); also elsewhere on the board
unnamed: C29.2, U11.11 (LDObyp1)
unnamed: C31.2, R10.1
unnamed: C32.2, U11.12 (LDObyp2)

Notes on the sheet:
100 MHz LVDS oscillator Timebase reference for entire board Invert output for routability
Test points for PLL status 3.3V logic levels
CLK_[3:0] to ADCs: 10 MHz, LVDS CLK_4 to ice40: 10 MHz, LVCMOS18 CLK_5 to Artix: 100 MHz, LVDS
Running PLL in single loop mode (Figure 17)
Could plausibly run VCO at 2400 MHz /24 = 100 MHz for Artix /240 = 10 MHz for ice40, ADCs /200 gives 12 MHz for FTDI For now, use separate oscillator for FTDI but integrating may save cost in final rev
Logic analyzer test point for PLL Microwire bus 3.3V3 logic levels
PLL2 charge pump external filter Internal components: C3 = 10 pF C4 = 10 pF R3 = 200 R4 = 200

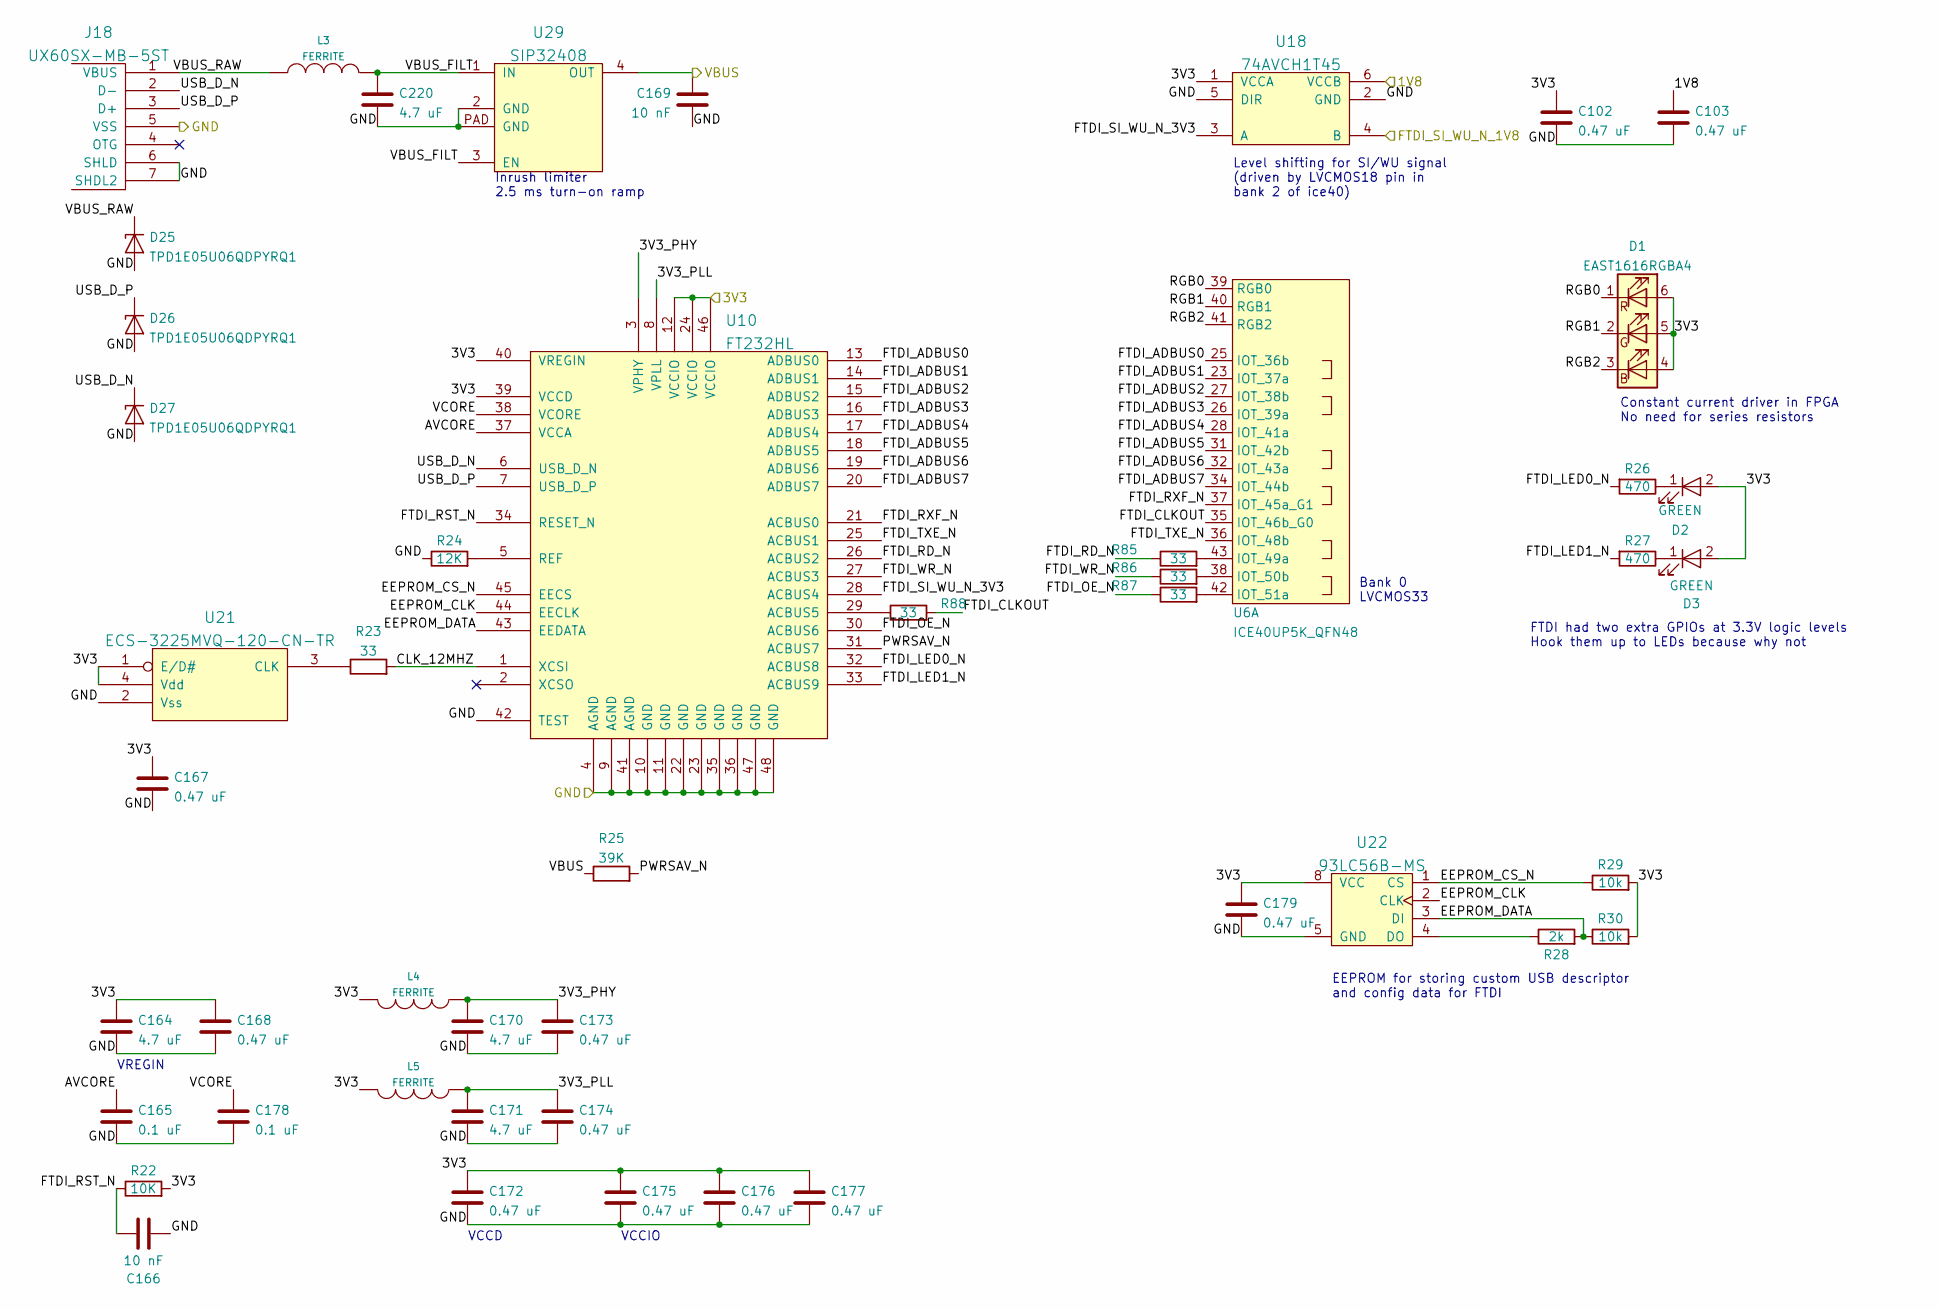
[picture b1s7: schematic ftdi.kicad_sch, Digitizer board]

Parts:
C102, C103, C167, C168, C172, C173, C174, C175, C176, C177, C179: 0.47 uF; EIA_0402_CAP_NOSILK
C164, C170, C171, C220: 4.7 uF; EIA_0603_CAP_NOSILK
C165, C178: 0.1 uF; EIA_0402_CAP_NOSILK
C166, C169: 10 nF; EIA_0603_CAP_NOSILK
D1: EAST1616RGBA4; LED_EVERLIGHT_EAST1616RGBA4
D2, D3: GREEN; EIA_0603_LED
D25, D26, D27: TPD1E05U06QDPYRQ1; DFN_2_1x0.6_TI_DPY
J18: UX60SX-MB-5ST; CONN_HIROSE_UX60S-MB-5ST_MINI_USB
L3, L4, L5: FERRITE; EIA_0603_INDUCTOR_NOSILK
R22: 10K; EIA_0402_RES_NOSILK
R23, R85, R86, R87, R88: 33; EIA_0402_RES_NOSILK
R24: 12K; EIA_0402_RES_NOSILK
R25: 39K; EIA_0402_RES_NOSILK
R26, R27: 470; EIA_0402_RES_NOSILK
R28: 2k; EIA_0402_RES_NOSILK
R29, R30: 10k; EIA_0402_RES_NOSILK
U6: ICE40UP5K_QFN48; QFN_48_0.5MM_7x7MM
U10: FT232HL; QFP_48_0.5MM
U18: 74AVCH1T45; DFN_6_0.5MM_1.45x1.00MM
U21: ECS-3225MVQ-120-CN-TR; OSCILLATOR_3.2x2.5
U22: 93LC56B-MS; SOP_8_0.5MM_3MM
U29: SIP32408; DFN_4_0.5MM_1.6x1.2MM

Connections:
/3V3: C102.1, C164.1, C167.1, C168.1, C172.1, C175.1, C176.1, C177.1, C179.1, D1.4 (BA), D1.5 (GA), D1.6 (RA), D2.2 (A), D3.2 (A), L4.2, L5.2, R22.2, R29.2, R30.2, U10.12 (VCCIO), U10.24 (VCCIO), U10.39 (VCCD), U10.40 (VREGIN), U10.46 (VCCIO), U18.1 (VCCA), U21.1 (E/D#), U21.4 (Vdd), U22.8 (VCC); also elsewhere on the board
/ADCs/FTDI_SI_WU_N: U18.4 (B); also elsewhere on the board
/D1V8: C103.1, U18.6 (VCCB); also elsewhere on the board
/FTDI USB interface/3V3_PHY: C170.1, C173.1, L4.1, U10.3 (VPHY)
/FTDI USB interface/3V3_PLL: C171.1, C174.1, L5.1, U10.8 (VPLL)
/FTDI USB interface/AVCORE: C165.1, U10.37 (VCCA)
/FTDI USB interface/CLK_12MHZ: R23.2, U10.1 (XCSI)
/FTDI USB interface/EEPROM_CLK: U10.44 (EECLK), U22.2 (CLK)
/FTDI USB interface/EEPROM_CS_N: R29.1, U10.45 (EECS), U22.1 (CS)
/FTDI USB interface/EEPROM_DATA: R28.2, R30.1, U10.43 (EEDATA), U22.3 (DI)
/FTDI USB interface/FTDI_ADBUS0: U6.25 (IOT_36b), U10.13 (ADBUS0)
/FTDI USB interface/FTDI_ADBUS1: U6.23 (IOT_37a), U10.14 (ADBUS1)
/FTDI USB interface/FTDI_ADBUS2: U6.27 (IOT_38b), U10.15 (ADBUS2)
/FTDI USB interface/FTDI_ADBUS3: U6.26 (IOT_39a), U10.16 (ADBUS3)
/FTDI USB interface/FTDI_ADBUS4: U6.28 (IOT_41a), U10.17 (ADBUS4)
/FTDI USB interface/FTDI_ADBUS5: U6.31 (IOT_42b), U10.18 (ADBUS5)
/FTDI USB interface/FTDI_ADBUS6: U6.32 (IOT_43a), U10.19 (ADBUS6)
/FTDI USB interface/FTDI_ADBUS7: U6.34 (IOT_44b), U10.20 (ADBUS7)
/FTDI USB interface/FTDI_CLKOUT: R88.2, U6.35 (IOT_46b_G0)
/FTDI USB interface/FTDI_LED0_N: R26.2, U10.32 (ACBUS8)
/FTDI USB interface/FTDI_LED1_N: R27.2, U10.33 (ACBUS9)
/FTDI USB interface/FTDI_OE_N: R87.1, U10.30 (ACBUS6)
/FTDI USB interface/FTDI_RD_N: R85.1, U10.26 (ACBUS2)
/FTDI USB interface/FTDI_RST_N: C166.1, R22.1, U10.34 (RESET_N)
/FTDI USB interface/FTDI_RXF_N: U6.37 (IOT_45a_G1), U10.21 (ACBUS0)
/FTDI USB interface/FTDI_SI_WU_N_3V3: U10.28 (ACBUS4), U18.3 (A)
/FTDI USB interface/FTDI_TXE_N: U6.36 (IOT_48b), U10.25 (ACBUS1)
/FTDI USB interface/FTDI_WR_N: R86.1, U10.27 (ACBUS3)
/FTDI USB interface/PWRSAV_N: R25.2, U10.31 (ACBUS7)
/FTDI USB interface/RGB0: D1.1 (RK), U6.39 (RGB0)
/FTDI USB interface/RGB1: D1.2 (GK), U6.40 (RGB1)
/FTDI USB interface/RGB2: D1.3 (BK), U6.41 (RGB2)
/FTDI USB interface/USB_D_N: D27.1 (K), J18.2 (D-), U10.6 (USB_D_N)
/FTDI USB interface/USB_D_P: D26.1 (K), J18.3 (D+), U10.7 (USB_D_P)
/FTDI USB interface/VBUS_FILT: C220.1, L3.1, U29.1 (IN), U29.3 (EN)
/FTDI USB interface/VBUS_RAW: D25.1 (K), J18.1 (VBUS), L3.2
/FTDI USB interface/VCORE: C178.1, U10.38 (VCORE)
/GND: C102.2, C103.2, C164.2, C165.2, C166.2, C167.2, C168.2, C169.2, C170.2, C171.2, C172.2, C173.2, C174.2, C175.2, C176.2, C177.2, C178.2, C179.2, C220.2, D25.2 (A), D26.2 (A), D27.2 (A), J18.5 (VSS), J18.6 (SHLD), J18.7 (SHDL2), R24.1, U10.4 (AGND), U10.9 (AGND), U10.10 (GND), U10.11 (GND), U10.22 (GND), U10.23 (GND), U10.35 (GND), U10.36 (GND), U10.41 (AGND), U10.42 (TEST), U10.47 (GND), U10.48 (GND), U18.2 (GND), U18.5 (DIR), U21.2 (Vss), U22.5 (GND), U29.2 (GND), U29.PAD (GND); also elsewhere on the board
/VBUS: C169.1, R25.1, U29.4 (OUT); also elsewhere on the board
unnamed: D2.1 (K), R26.1
unnamed: D3.1 (K), R27.1
unnamed: R23.1, U21.3 (CLK)
unnamed: R24.2, U10.5 (REF)
unnamed: R28.1, U22.4 (DO)
unnamed: R85.2, U6.43 (IOT_49a)
unnamed: R86.2, U6.38 (IOT_50b)
unnamed: R87.2, U6.42 (IOT_51a)
unnamed: R88.1, U10.29 (ACBUS5)

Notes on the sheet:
EEPROM for storing custom USB descriptor and config data for FTDI
VREGIN
Inrush limiter 2.5 ms turn-on ramp
FTDI had two extra GPIOs at 3.3V logic levels Hook them up to LEDs because why not
Level shifting for SI/WU signal (driven by LVCMOS18 pin in bank 2 of ice40)
VCCIO
Bank 0 LVCMOS33
VCCD
Constant current driver in FPGA No need for series resistors
